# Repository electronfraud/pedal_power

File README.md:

# Pedal Power

This is a power supply for guitar pedals. It's a basic AC-DC converter that I built to get
comfortable with rectifying mains AC. Unlike most AC adapters, it's a linear power supply, not
switching. The reason I built it this way is because I wanted low noise since this is for an
audio application. It's also much simpler than a switching supply. The tradeoff is that it's
bigger, less efficient, and hotter, but that's an acceptable trade for a pedalboard. I used
exclusively through-hole parts to make it easier to build (and to repair when it eventually
breaks).

**N.B.:** For reasons lost to the sands of time, guitar pedal power jacks are wired **center
negative**. This is not how the vast majority of other DC receptacles are wired. Keep that in
mind if you decide to make this and want to plug it into something normal.

## Specifications

- Input: 115/120V, 50/60Hz AC
- Output: 9V DC, center negative, up to 500mA total across three jacks
- Reassuring power light

There's room on the board for a 12V/1A AC output&mdash;I had an ancient tube compressor that needed
this&mdash;but I didn't end up populating that in the actual build.

## Enclosure

I enclosed the PCB and transformer in a [Hammond 1455KHD1201BK](https://www.hammfg.com/electronics/small-case/extruded/1455nhd).
The case is attached to the ground terminal on the power entry module (see "Other Parts" below).

For heat dissipation, the regulator (U1) is attached to the enclosure with a strip of aluminum I
cut from a soda can and some thermally conductive double-sided tape.

## Other Parts

A couple parts aren't specified in the schematic:

- Transformer: Hammond 166GD12
- Power entry module: Schaffner FN285-2-06

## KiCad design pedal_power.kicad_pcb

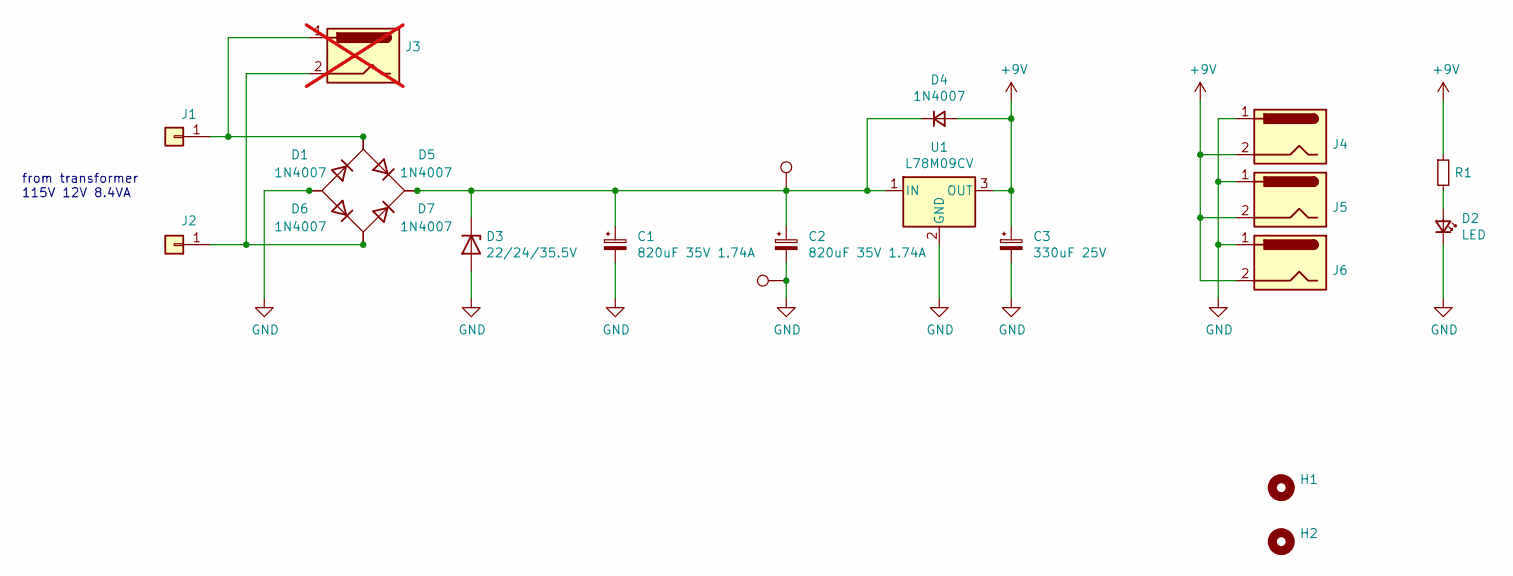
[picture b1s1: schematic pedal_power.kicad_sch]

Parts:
C1, C2: 820uF 35V 1.74A; CP_Radial_D12.5mm_P5.00mm
C3: 330uF 25V; CP_Radial_D8.0mm_P3.50mm
D1, D4, D5, D6, D7: 1N4007; D_DO-41_SOD81_P10.16mm_Horizontal
D2: LED; LED_D3.0mm
D3: 22/24/35.5V; D_P600_R-6_P12.70mm_Horizontal
H1, H2: MountingHole; MountingHole_2.2mm_M2
J1: L; SolderWirePad_1x01_Drill2mm
J2: N; SolderWirePad_1x01_Drill2mm
J3: Barrel_Jack; BarrelJack_CUI_PJ-102AH_Horizontal; not fitted
J4, J5, J6: Barrel_Jack; BarrelJack_CUI_PJ-102AH_Horizontal
R1: R_Small; R_Axial_DIN0309_L9.0mm_D3.2mm_P5.08mm_Vertical
TP1, TP2: TestPoint; TestPoint_THTPad_D2.0mm_Drill1.0mm
U1: L78M09CV; TO-220-3_Horizontal_TabDown

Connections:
+9V: C3.1, D4.2 (A), J4.2, J5.2, J6.2, R1.1, U1.3 (OUT)
GND: C1.2, C2.2, C3.2, D1.2 (A), D2.1 (K), D3.2 (A), D6.2 (A), J4.1, J5.1, J6.1, TP2.1, U1.2 (GND)
unnamed: C1.1, C2.1, D3.1 (K), D4.1 (K), D5.1 (K), D7.1 (K), TP1.1, U1.1 (IN)
unnamed: D1.1 (K), D5.2 (A), J1.1, J3.1
unnamed: D2.2 (A), R1.2
unnamed: D6.1 (K), D7.2 (A), J2.1, J3.2

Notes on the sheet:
from transformer 115V 12V 8.4VA

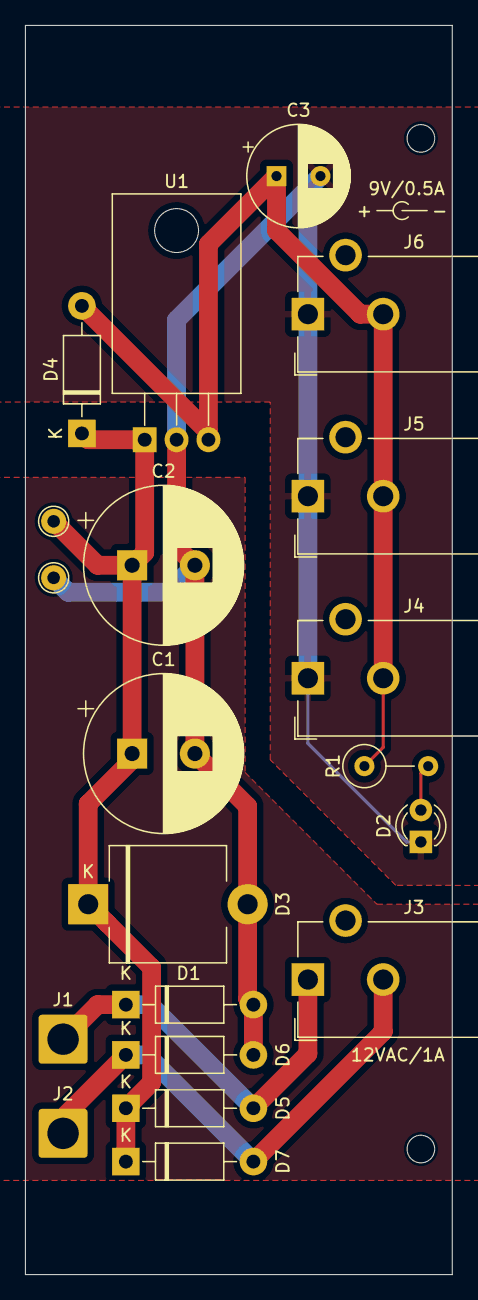
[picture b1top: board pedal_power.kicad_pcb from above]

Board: 2 copper layers, 34.0 x 99.5 mm, 22 parts (0 on the bottom side), 6 nets.

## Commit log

2023-03-01 fix PJ-102AH 3d model
2023-03-02 tidy up schematic
2023-03-02 add d_small_45 symbol
2023-03-04 update to kicad 7 and add plot workflow
2023-03-04 plot schematics
